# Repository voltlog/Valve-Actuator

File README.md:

# 10ch Valve Actuator (Tasmota compatible)
I designed this 10 channel valve actuator board to be able to control up to 10 electrical valve actuators for my floor heating system. It is based on an ESP32 which makes it Tasmota/MQTT compatible and this allows me to easily integrate it into my HomeaAssistant server. For more information check out [Voltlog #383](https://youtu.be/kZS3ggG0QJI).

If you are looking for sources of previous revisions (revA, revB, revC) checkout the different branches of this repo.

To flash the ESP32 you can use a VoltLink usb/serial converter or you can use your own usb-serial converter module through the on-board JST-SH 1.0mm pitch 6 pin connector. After loading the initial firmware, you can update the firmware via OTA. By default board will ship loaded with Tasmota. 

If you would like to order one of these boards ready assembled, check out my [Tindie store](https://www.tindie.com/products/voltlog/tasmota-esp32-floor-heating-valve-controller/).

## Tasmota template revD (do not use this for previous revisions)
{"NAME":"Voltlog Valve Actuator revD","GPIO":[0,3200,288,3232,0,0,0,0,0,228,229,227,234,0,226,225,0,640,608,224,0,232,231,230,0,0,0,0,233,0,32,0,0,0,0,0],"FLAG":0,"BASE":1}

## WARNING
This board has high-voltage AC present which may cause severe personal injury or death if not handled with care. If you are in doubt, please ask for a profesional to install the system for you.

## Changelog revD
- Added support for powering valves with separate voltage input.
- Switched multiple components to SMD variant for DFM purposes.
- Switched to using JST SH connector for expansion GPIO.

For more defails on revD changes checkout this video [Voltlog #467](https://youtu.be/UIELTaJPIKA).

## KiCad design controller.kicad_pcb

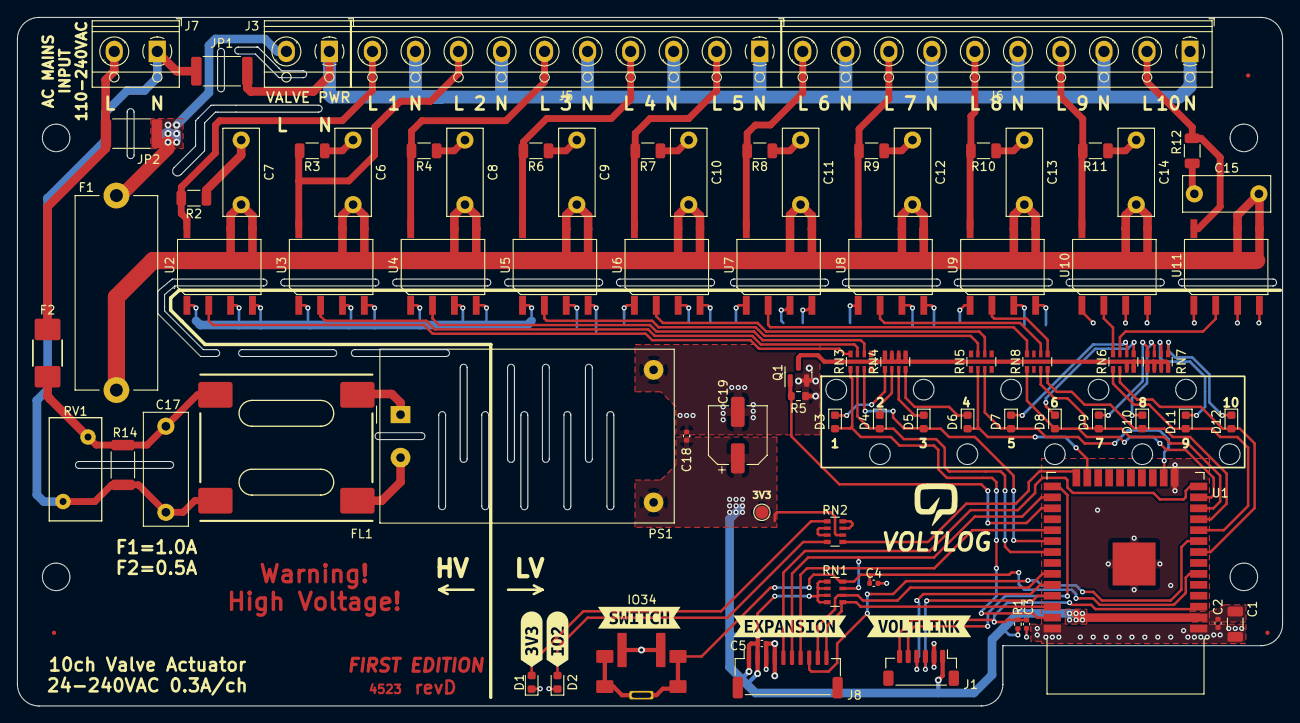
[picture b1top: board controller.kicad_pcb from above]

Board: 2 copper layers, 147.0 x 80.0 mm, 93 parts (0 on the bottom side), 78 nets.

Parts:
C1: 22uF; C_1206_3216Metric
C2, C3, C4, C5, C18: 0.1uF; C_0402_1005Metric
C6, C7, C8, C9, C10, C11, C12, C13, C14, C15: 10nF; C_Rect_L10.0mm_W4.0mm_P7.50mm_MKS4
C17: 0.1uF; C_Rect_L13.0mm_W5.0mm_P10.00mm_FKS3_FKP3_MKS4
C19: 220uF; CP_Elec_6.3x7.7
D1: 3V3; LED_0603_1608Metric
D2: USER; LED_0603_1608Metric
D3: CH1; LED_0603_1608Metric
D4: CH2; LED_0603_1608Metric
D5: CH3; LED_0603_1608Metric
D6: CH4; LED_0603_1608Metric
D7: CH5; LED_0603_1608Metric
D8: CH6; LED_0603_1608Metric
D9: CH7; LED_0603_1608Metric
D10: CH8; LED_0603_1608Metric
D11: CH9; LED_0603_1608Metric
D12: CH10; LED_0603_1608Metric
F1: 1A 250VAC; Fuseholder_Cylinder-5x20mm_Stelvio-Kontek_PTF78_Horizontal_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
F2: 0.5A 250VAC; Fuse_2410
FID1, FID2, FID3: Fiducial; Fiducial_0.5mm_Mask1mm
FL1: 15mH; PSSQAQ1212-153M
H3, H4, H5, H6: MountingHole; MountingHole_3.2mm_M3_DIN965
J1: VoltLink_target; VoltLink-vertical
J3: VALVE IN; TerminalBlock_1x02_P5.00mm_Horizontal
J5, J6: OUTPUT; TerminalBlock_1x10_P5.00mm_Horizontal
J7: AC IN; TerminalBlock_1x02_P5.00mm_Horizontal
J8: Expansion; JST_SH_SM10B-SRSS-TB_1x10-1MP_P1.00mm_Horizontal
JP1: NEUTRAL; R_2512_6332Metric
JP2: LIVE; R_2512_6332Metric
N1: Housing; BRT-80005
N2: LightPipe; 1272.1020
PS1: HLK-PM03; Converter_ACDC_HiLink_HLK-PMxx
Q1: AO3400A; SOT-23
R1: 10K; R_0402_1005Metric
R2, R3, R4, R6, R7, R8, R9, R10, R11, R12: 47R; R_1206_3216Metric
R5: 10K; R_0603_1608Metric
R14: 1M; R_2010_5025Metric
RN1: 4K7; R_Array_Convex_4x0603
RN2, RN3, RN4, RN5, RN6, RN7, RN8: 100R; R_Array_Convex_4x0603
RV1: 10D561K; RV_Disc_D12mm_W6.1mm_P7.5mm
SW1: USER; TS1045AD
TP5: 3V3; TestPoint_Pad_D1.5mm
U1: ESP32-WROOM-32D; ESP32-WROOM-32
U2, U3, U4, U5, U6, U7, U8, U9, U10, U11: BC2213A; SOIC-7
V1: VOLTLOG_LOGO; voltlog_silk_5mm
kibuzzard-654A05B0: G***; kibuzzard-654A05B0
kibuzzard-654A05C3: G***; kibuzzard-654A05C3
kibuzzard-654A05E9: G***; kibuzzard-654A05E9
kibuzzard-654A0597: G***; kibuzzard-654A0597
kibuzzard-654A0611: G***; kibuzzard-654A0611

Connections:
+3V3: C1.1, C2.2, C5.1, C18.2, C19.1, J1.1 (3V3), J8.1, J8.2, PS1.4 (+Vout), R1.2, RN1.5 (R4.2), RN1.6 (R3.2), RN1.7 (R2.2), RN1.8 (R1.2), RN2.2 (R2.1), TP5.1, U1.2 (VDD)
/240V_LIVE: F2.2, J7.2, JP2.1 (A)
/240V_NEUTRAL: C17.2, FL1.1, J7.1, JP1.1 (A), R14.2, RV1.2
/ACDC Converter/240V_FUSED_LIVE: C17.1, F2.1, FL1.2, R14.1, RV1.1
/EN: C3.1, J1.6 (EN), R1.1, U1.3 (EN)
/IO0: J1.5 (IO0), U1.25 (IO0)
/IO2: RN2.1 (R1.1), U1.24 (IO2)
/IO4: J8.6, RN1.3 (R3.1), U1.26 (IO4)
/IO5: J8.7, U1.29 (IO5)
/IO12: J8.5, U1.14 (IO12)
/IO13: D7.2 (A), RN5.3 (R3.1), U1.16 (IO13)
/IO14: D8.2 (A), RN8.1 (R1.1), U1.13 (IO14)
/IO15: D6.2 (A), RN5.2 (R2.1), U1.23 (IO15)
/IO16: Q1.1 (G), R5.2, U1.27 (IO16)
/IO18: D5.2 (A), RN3.3 (R3.1), U1.30 (IO18)
/IO19: D4.2 (A), RN3.2 (R2.1), U1.31 (IO19)
/IO23: D3.2 (A), RN3.1 (R1.1), U1.37 (IO23)
/IO25: D11.2 (A), RN6.1 (R1.1), U1.10 (IO25)
/IO26: D10.2 (A), RN8.4 (R4.1), U1.11 (IO26)
/IO27: D9.2 (A), RN8.3 (R3.1), U1.12 (IO27)
/IO32: D12.2 (A), RN6.2 (R2.1), U1.8 (IO32)
/IO33: J8.8, U1.9 (IO33)
/IO34: C4.1, RN1.4 (R4.1), SW1.1, U1.6 (IO34)
/LIVE: F1.1, J3.2, JP2.2 (B)
/NEUTRAL: J3.1, J5.1, J5.3, J5.5, J5.7, J5.9, J6.1, J6.3, J6.5, J6.7, J6.9, JP1.2 (B)
/RXD: J1.4 (RXD), U1.34 (RXD0/IO3)
/Relay/TRIAC_FUSED_LIVE: C6.2, C7.2, C8.2, C9.2, C10.2, C11.2, C12.2, C13.2, C14.2, C15.2, F1.2, U2.5, U2.6, U3.5, U3.6, U4.5, U4.6, U5.5, U5.6, U6.5, U6.6, U7.5, U7.6, U8.5, U8.6, U9.5, U9.6, U10.5, U10.6, U11.5, U11.6
/SCL: J8.10, RN1.1 (R1.1), U1.36 (IO22)
/SDA: J8.9, RN1.2 (R2.1), U1.33 (IO21)
/TXD: J1.3 (TXD), U1.35 (TXD0/IO1)
GND: C1.2, C2.1, C3.2, C4.2, C5.2, C18.1, C19.2, D1.1 (K), D2.1 (K), J1.2 (GND), J8.3, J8.4, PS1.3 (-Vout), Q1.2 (S), R5.1, SW1.2, U1.1 (GND), U1.15 (GND), U1.38 (GND), U1.39 (GND), U2.1, U2.3, U2.4, U3.1, U3.3, U3.4, U4.1, U4.3, U4.4, U5.1, U5.3, U5.4, U6.1, U6.3, U6.4, U7.1, U7.3, U7.4, U8.1, U8.3, U8.4, U9.1, U9.3, U9.4, U10.1, U10.3, U10.4, U11.1, U11.3, U11.4
unnamed: C6.1, R3.1
unnamed: C7.1, R2.1
unnamed: C8.1, R4.1
unnamed: C9.1, R6.1
unnamed: C10.1, R7.1
unnamed: C11.1, R8.1
unnamed: C12.1, R9.1
unnamed: C13.1, R10.1
unnamed: C14.1, R11.1
unnamed: C15.1, R12.1
unnamed: D1.2 (A), RN2.5 (R4.2)
unnamed: D2.2 (A), RN2.8 (R1.2)
unnamed: D3.1 (K), RN4.1 (R1.1)
unnamed: D4.1 (K), RN4.2 (R2.1)
unnamed: D5.1 (K), RN4.3 (R3.1)
unnamed: D6.1 (K), RN4.4 (R4.1)
unnamed: D7.1 (K), RN6.6 (R3.2)
unnamed: D8.1 (K), RN6.5 (R4.2)
unnamed: D9.1 (K), RN7.8 (R1.2)
unnamed: D10.1 (K), RN7.7 (R2.2)
unnamed: D11.1 (K), RN7.6 (R3.2)
unnamed: D12.1 (K), RN7.5 (R4.2)
unnamed: J5.2, R7.2, U6.7
unnamed: J5.4, R6.2, U5.7
unnamed: J5.6, R4.2, U4.7
unnamed: J5.8, R3.2, U3.7
unnamed: J5.10, R2.2, U2.7
unnamed: J6.2, R12.2, U11.7
unnamed: J6.4, R11.2, U10.7
unnamed: J6.6, R10.2, U9.7
unnamed: J6.8, R9.2, U8.7
unnamed: J6.10, R8.2, U7.7
unnamed: FL1.3, PS1.1 (AC/L)
unnamed: FL1.4, PS1.2 (AC/N)
unnamed: Q1.3 (D), RN4.5 (R4.2), RN4.6 (R3.2), RN4.7 (R2.2), RN4.8 (R1.2), RN6.3 (R3.1), RN6.4 (R4.1), RN7.1 (R1.1), RN7.2 (R2.1), RN7.3 (R3.1), RN7.4 (R4.1)
unnamed: RN2.6 (R3.2), RN2.7 (R2.2)
unnamed: RN2.3 (R3.1), RN2.4 (R4.1)
unnamed: RN3.8 (R1.2), U2.2
unnamed: RN3.7 (R2.2), U3.2
unnamed: RN3.6 (R3.2), U4.2
unnamed: RN5.7 (R2.2), U5.2
unnamed: RN5.6 (R3.2), U6.2
unnamed: RN6.8 (R1.2), U10.2
unnamed: RN6.7 (R2.2), U11.2
unnamed: RN8.8 (R1.2), U7.2
unnamed: RN8.6 (R3.2), U8.2
unnamed: RN8.5 (R4.2), U9.2

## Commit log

2021-10-17 Added tasmota template
2021-11-09 Updated Readme
    Updated readme to mention silkscreen issue on J6.
2021-12-10 revB release
2021-12-12 RevC initial release
2021-12-12 Updated README for revC
2022-04-04 Added schematic in PDF format
2022-04-11 Added quick start guide
2022-04-11 Updated quick start guide
2023-02-02 Updated quick start guide
    Updated quick start guide with new information regarding expansion port GPIO assignments.
2023-12-22 Release revE First Edition
2023-12-22 RevD First Edition release
2023-12-22 cleanup revD-first
2023-12-22 Cleanup README
2023-12-22 Cleanup revD
2023-12-22 Cleaup revD
2024-01-24 added missing block
2024-01-24 added first edition branch
